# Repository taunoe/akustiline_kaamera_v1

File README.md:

# Akustilise kaamera projekt

## Andur

- 16 mikrofoni
- Mikrofonid on paigutatud päevalillespiraali (Vogeli spiraal).
- Jaotuvad ühtlaselt üle pinna ja ükski vahekaugus ei kordu.

### Koordinaadid

Nullpunkt on kaamera ava keskel, mõõdud millimeetrites mikrofoni heliava keskkohani. Sisemine raadius on 22 mm ja välimine 80 mm.

Mikrofon|x	  |y	
--------|-----|-----
M1	    | 22,0|  0,0	
M2	    |−21,9| 20,0	
M3	    |  3,1|−35,5
M4	    | 24,8| 32,4	
M5	    |−44,7| −7,9	
M6	    | 41,8|−26,6
M7	    |−13,9| 51,6
M8	    |−26,2|−50,6
M9	    | 56,7| 20,7
M10	    |−58,7|	24,2
M11	    | 28,2|−60,3
M12	    | 20,8|	66,3
M13	    |−62,5|−36,2
M14	    | 73,2|−16,1
M15	    |−44,6|	63,4
M16	    |−10,3|−79,3

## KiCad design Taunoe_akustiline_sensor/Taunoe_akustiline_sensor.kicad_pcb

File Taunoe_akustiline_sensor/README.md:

# Taunoe akustiline andur

## Komponendid

- TI SN74LVC244APWR, TSSOP-20, C7668, https://www.lcsc.com/product-detail/C7668.html
- TDK InvenSense ICS-43434,LGA-6(3.5x2.7), C5656610, https://www.lcsc.com/product-detail/C5656610.html
- 100nF, 0402, C131394, https://www.lcsc.com/product-detail/C131394.html
- 4.7uF, 0603, C19666, https://www.lcsc.com/product-detail/C19666.html
- 10uF, 0805, C15850, https://www.lcsc.com/product-detail/C15850.html
- 33ohm, 0402, C138002, https://www.lcsc.com/product-detail/C138002.html
- 100K, 0402, C60491, https://www.lcsc.com/product-detail/C60491.html

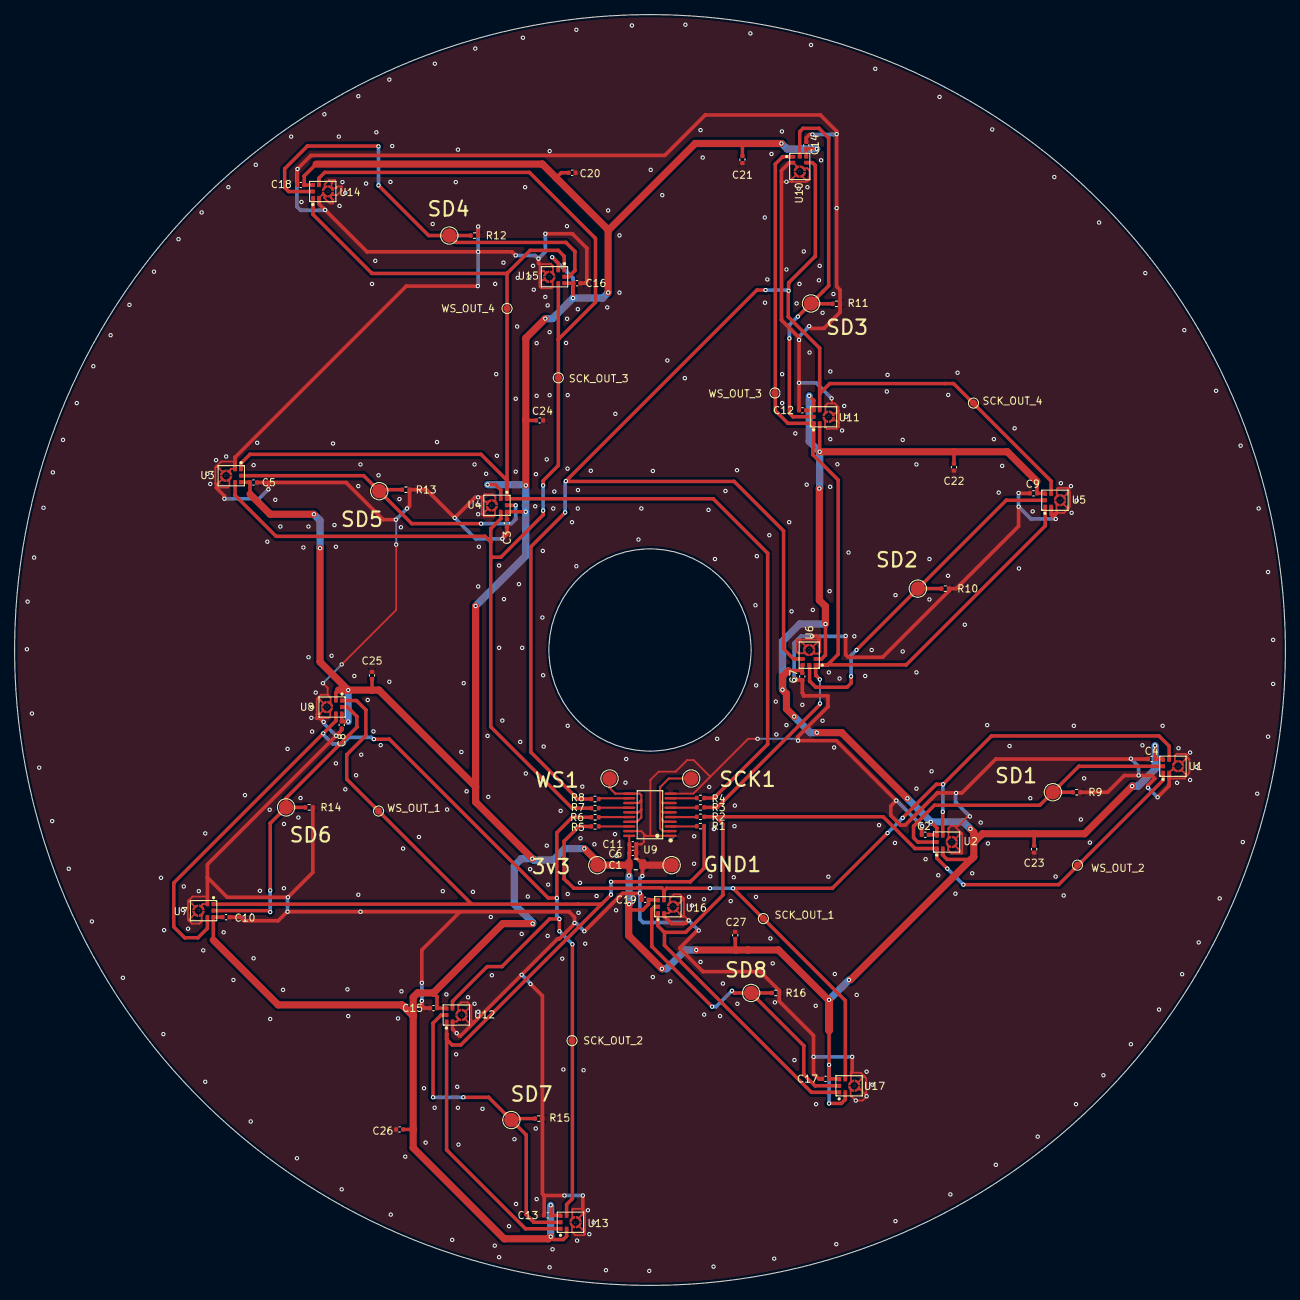
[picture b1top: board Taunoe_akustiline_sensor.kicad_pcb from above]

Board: 2 copper layers, 176.0 x 176.0 mm, 80 parts (0 on the bottom side), 28 nets.

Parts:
3v3: TestPoint_Pad_D2.0mm
C1: 10uF; C_0805_2012Metric
C2, C3, C4, C5, C6, C7, C8, C9, C10, C11, C12, C13, C14, C15, C16, C17, C18, C19: 100nF; C_0402_1005Metric
C20, C21, C22, C23, C24, C25, C26, C27: 4.7 uF; C_0402_1005Metric
GND1: TestPoint_Pad_D2.0mm
R1, R2, R3, R4, R5, R6, R7, R8: R33; R_0402_1005Metric
R9, R10, R11, R12, R13, R14, R15, R16: 100K; R_0402_1005Metric
SCK1: TestPoint_Pad_D2.0mm
SCK_OUT_1, SCK_OUT_2, SCK_OUT_3, SCK_OUT_4: TestPoint_Pad_D1.0mm
SD1, SD2, SD3, SD4, SD5, SD6, SD7, SD8: TestPoint_Pad_D2.0mm
U1, U2, U3, U4, U5, U6, U7, U8, U10, U11, U12, U13, U14, U15, U16, U17: ICS-43434_C5656610; MIC-SMD_6P-L3.5-W2.7-P0.90-BL
U9: SN74LVC244APWR; TSSOP-20_L6.5-W4.4-P0.65-LS6.4-BL
WS1: TestPoint_Pad_D2.0mm
WS_OUT_1, WS_OUT_2, WS_OUT_3, WS_OUT_4: TestPoint_Pad_D1.0mm

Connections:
+3.3V: 3v3.1 (1_1), C1.1, C2.1, C3.1, C4.1, C5.1, C6.1, C7.1, C8.1, C9.1, C10.1, C11.1, C12.1, C13.1, C14.1, C15.1, C16.1, C17.1, C18.1, C19.1, C20.1, C21.1, C22.1, C23.1, C24.1, C25.1, C26.1, C27.1, U1.5 (VDD), U2.2 (LR), U2.5 (VDD), U3.5 (VDD), U4.2 (LR), U4.5 (VDD), U5.5 (VDD), U6.2 (LR), U6.5 (VDD), U7.5 (VDD), U8.2 (LR), U8.5 (VDD), U9.20 (VCC), U10.5 (VDD), U11.2 (LR), U11.5 (VDD), U12.5 (VDD), U13.2 (LR), U13.5 (VDD), U14.5 (VDD), U15.2 (LR), U15.5 (VDD), U16.5 (VDD), U17.2 (LR), U17.5 (VDD)
/SCK_IN: SCK1.1 (1_1), U9.2 (1A1), U9.4 (1A2), U9.6 (1A3), U9.8 (1A4)
/SCK_OUT_1: R5.2, SCK_OUT_1.1 (1_1), U1.4 (SCK), U2.4 (SCK), U16.4 (SCK), U17.4 (SCK)
/SCK_OUT_2: R6.2, SCK_OUT_2.1 (1_1), U7.4 (SCK), U8.4 (SCK), U12.4 (SCK), U13.4 (SCK)
/SCK_OUT_3: R7.2, SCK_OUT_3.1 (1_1), U3.4 (SCK), U4.4 (SCK), U14.4 (SCK), U15.4 (SCK)
/SCK_OUT_4: R8.2, SCK_OUT_4.1 (1_1), U5.4 (SCK), U6.4 (SCK), U10.4 (SCK), U11.4 (SCK)
/SD_IN_1: R9.1, SD1.1 (1_1), U1.6 (SD), U2.6 (SD)
/SD_IN_2: R10.1, SD2.1 (1_1), U5.6 (SD), U6.6 (SD)
/SD_IN_3: R11.1, SD3.1 (1_1), U10.6 (SD), U11.6 (SD)
/SD_IN_4: R12.1, SD4.1 (1_1), U14.6 (SD), U15.6 (SD)
/SD_IN_5: R13.1, SD5.1 (1_1), U3.6 (SD), U4.6 (SD)
/SD_IN_6: R14.1, SD6.1 (1_1), U7.6 (SD), U8.6 (SD)
/SD_IN_7: R15.1, SD7.1 (1_1), U12.6 (SD), U13.6 (SD)
/SD_IN_8: R16.1, SD8.1 (1_1), U16.6 (SD), U17.6 (SD)
/WS_IN: U9.11 (2A1), U9.13 (2A2), U9.15 (2A3), U9.17 (2A4), WS1.1 (1_1)
/WS_OUT_1: R1.1, U7.1 (WS), U8.1 (WS), U12.1 (WS), U13.1 (WS), WS_OUT_1.1 (1_1)
/WS_OUT_2: R2.1, U1.1 (WS), U2.1 (WS), U16.1 (WS), U17.1 (WS), WS_OUT_2.1 (1_1)
/WS_OUT_3: R3.1, U5.1 (WS), U6.1 (WS), U10.1 (WS), U11.1 (WS), WS_OUT_3.1 (1_1)
/WS_OUT_4: R4.1, U3.1 (WS), U4.1 (WS), U14.1 (WS), U15.1 (WS), WS_OUT_4.1 (1_1)
GND: C1.2, C2.2, C3.2, C4.2, C5.2, C6.2, C7.2, C8.2, C9.2, C10.2, C11.2, C12.2, C13.2, C14.2, C15.2, C16.2, C17.2, C18.2, C19.2, C20.2, C21.2, C22.2, C23.2, C24.2, C25.2, C26.2, C27.2, GND1.1 (1_1), R9.2, R10.2, R11.2, R12.2, R13.2, R14.2, R15.2, R16.2, U1.2 (LR), U1.3 (GND), U2.3 (GND), U3.2 (LR), U3.3 (GND), U4.3 (GND), U5.2 (LR), U5.3 (GND), U6.3 (GND), U7.2 (LR), U7.3 (GND), U8.3 (GND), U9.1 (1OE#), U9.10 (GND), U9.19 (2OE#), U10.2 (LR), U10.3 (GND), U11.3 (GND), U12.2 (LR), U12.3 (GND), U13.3 (GND), U14.2 (LR), U14.3 (GND), U15.3 (GND), U16.2 (LR), U16.3 (GND), U17.3 (GND)
unnamed: R5.1, U9.18 (1Y1)
unnamed: R6.1, U9.16 (1Y2)
unnamed: R7.1, U9.14 (1Y3)
unnamed: R8.1, U9.12 (1Y4)
unnamed: R4.2, U9.9 (2Y1)
unnamed: R3.2, U9.7 (2Y2)
unnamed: R2.2, U9.5 (2Y3)
unnamed: R1.2, U9.3 (2Y4)

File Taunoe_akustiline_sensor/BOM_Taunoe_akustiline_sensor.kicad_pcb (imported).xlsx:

| Designator | Quantity | Value | Footprint | Package | Manufacturer | MPN | DNP | Mount_Type | Description | LCSC Part
1 | C1 | 1 | 10uF | C_0805_2012Metric | 0805 | Samsung Electro-Mechanics | CL21B106KOQNNNE |  | smt | Unpolarized capacitor | C95841
2 | C10, C11, C12, C13, C14, C15, C16, C17, C18, C19, C2, C3, C4, C5, C6, C7, C8, C9 | 18 | 100nF | C_0402_1005Metric | 0402 | Samsung Electro-Mechanics | CL05B104KO5NNNC |  | smt | Unpolarized capacitor | C1525
3 | C20, C21, C22, C23, C24, C25, C26, C27 | 8 | 4.7 uF | C_0402_1005Metric | 0402 | Samsung Electro-Mechanics | CL05A475KP5NRNC |  | smt | Unpolarized capacitor | C368809
4 | R1, R2, R3, R4, R5, R6, R7, R8 | 8 | R33 | R_0402_1005Metric | 0402 | YAGEO | RC0402FR-0733RL |  | smt | Resistor | C138002
5 | R10, R11, R12, R13, R14, R15, R16, R9 | 8 | 100K | R_0402_1005Metric | 0402 | YAGEO | RC0402FR-07100KL |  | smt | Resistor | C60491
6 | U1, U10, U11, U12, U13, U14, U15, U16, U17, U2, U3, U4, U5, U6, U7, U8 | 16 | ICS-43434_C5656610 | MIC-SMD_6P-L3.5-W2.7-P0.90-BL | LGA-6(3.5x2.7) | TDK InvenSense | ICS-43434 |  | smt | ICS-43434_C5656610 | C5656610
7 | U9 | 1 | SN74LVC244APWR | TSSOP-20_L6.5-W4.4-P0.65-LS6.4-BL | TSSOP-20 | TI | SN74LVC244APWR |  | smt | SN74LVC244APWR | C7668
8 | SCK_OUT_1, SCK_OUT_2, SCK_OUT_3, SCK_OUT_4, WS_OUT_1, WS_OUT_2, WS_OUT_3, WS_OU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 | 8 | ~ | TestPoint_Pad_D1.0mm |  |  |  | DNP | tht | test point
9 | 3v3, GND1, SCK1, SD1, SD2, SD3, SD4, SD5, SD6, SD7, SD8, WS1 | 12 | ~ | TestPoint_Pad_D2.0mm |  |  |  | DNP | tht | test point
